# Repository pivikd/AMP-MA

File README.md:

# Project Status

   **AMP-AM is currently in the early development phase and is considered unstable. The first stable release is scheduled for Q4 2026**
   
   **The project is currently in the pre-alpha stage – creating the first prototype**

# AMP-AM (AMP Modus Aequale)

AMP-AM (standing for Modus Aequale, signifying a rhythmic, ideal tone and modular structure) is an open-source, transistor-based guitar combo amplifier project. It is designed to bridge the gap between solid-state reliability and the organic, harmonic richness of vacuum tube sound.

The project focuses on a modular architecture, originally developed as a high-fidelity upgrade for the **Epiphone 15C** PCB. By utilizing independent blocks, AMP-AM allows for seamless customization and easier adaptation to various amp enclosures.

This project is designed and maintained by: [Danylo Pyvovarov](https://github.com/pivikd).

   1. [Key Features](#key-features)
   1. [Signal Chain](#signal-chain)
   1. [Integrated Tone Stacks](#integrated-tone-stacks)
<!-- 1. [Integrated Effects Modules](#integrated-effects-modules) -->
## Key Features
   - **Tube-like Architecture**: Uses **Mu-amp** based cascades with **2SK30A** transistors to achieve a warm, organic sound and harmonic saturation that mimics vacuum tube behavior.

   - **Dual Input Support**: Designed to handle two guitars simultaneously.

   - **Legendary Tone Stacks**: Features a 3-band EQ based on the classic tone stacks([Integrated Tone Stacks](#integrated-tone-stacks)).

   - **Integrated Compression**: Built-in compressor block based on the vintage **Ibanez CP835** circuitry.

   <!-- - **Modular Design**: Optimized for easy integration into different amp cabinets or for swapping internal effect modules. -->

## Signal Chain
   1. Input buffer
   1. Preamp ([Mu-AMP](https://www.muzique.com/amz/mini.htm))
   1. Compressor ([Ibanez CP835](https://www.scribd.com/document/976348354/Ibanez-CP835-Schematic))
   1. Tone Stack
   1. Recovery Stage
   1. Power Amp ([LM1875](https://www.ti.com/lit/ds/symlink/lm1875.pdf))

<!-- ## Integrated Effects Modules
|       Effect      |   based on   |  Status  |
|-------------------|--------------|---------|
| Compressor        | Ibanez CP835 |  done   |
<!-- | Over Drive        | Boss OD3     | planned  |
| Chorus            | Boss Ch1     | planned  | --> 

## Integrated Tone Stacks
   - Fender Treble-Middle-Bass
   - Marshall ([JCM900 2100 SL-X](https://stompboxelectronics.com/2023/12/16/the-marshall-tone-stacks/))
   - Dumble Rock

      Own:
   - TS0 (based on Marshall JCM900 2100 SL-x)
   - TS1 (based on Dumble Rock)

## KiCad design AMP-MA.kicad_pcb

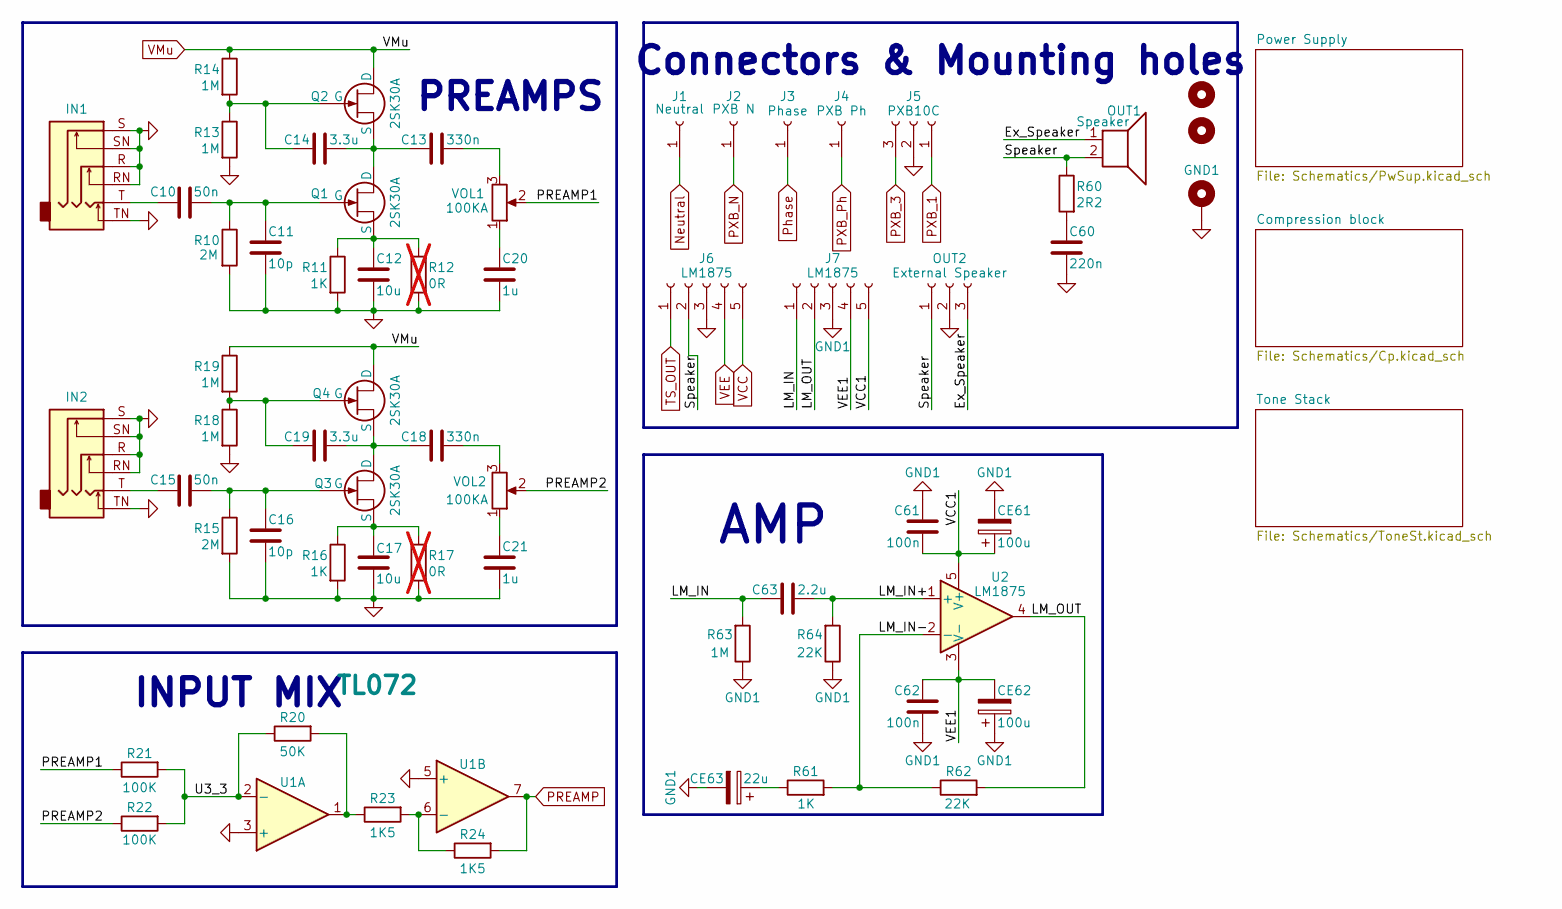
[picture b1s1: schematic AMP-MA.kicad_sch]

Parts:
C10, C15: 50n; C_disc_D7_W2.5_P5
C11, C16: 10p; C_disc_D7_W2.5_P5
C12, C17: 10u; C_disc_D7_W2.5_P5
C13, C18: 330n; C_disc_D7_W2.5_P5
C14, C19: 3.3u; C_disc_D7_W2.5_P5
C20, C21: 1u; C_disc_D7_W2.5_P5
C60: 220n; C_disc_D7_W2.5_P5
C61, C62: 100n; C_disc_D7_W2.5_P5
C63: 2.2u; C_disc_D7_W2.5_P5
CE61, CE62: 100u; CP_Radial_D6.3mm_P2.50mm
CE63: 22u; CP_Radial_D5.0mm_P2.50mm
GND1: MountingHole_Pad; MountingHole_2.2mm_M2_DIN965_Pad
H1, H2: MountingHole; MountingHole_2.2mm_M2
IN1, IN2: Jack_3_6pin
J1: Neutral; connector
J2: PXB N; connector
J3: Phase
J4: PXB Ph
J5: PXB10C; JST_XH_B3B-XH-A_1x03_P2.50mm_Vertical
J6, J7: LM1875; JST_XH_B5B-XH-A_1x05_P2.50mm_Vertical
OUT1: Speaker; PinSocket_1x02_P2.54mm_Vertical
OUT2: External Speaker; JST_XH_B3B-XH-A_1x03_P2.50mm_Vertical
Q1, Q2, Q3, Q4: 2SK30A; TO-92_Inline_Wide
R10, R15: 2M; R_Axial_DIN0207_L6.3mm_D2.5mm_P10.16mm_Horizontal
R11, R16, R61: 1K; R_Axial_DIN0207_L6.3mm_D2.5mm_P10.16mm_Horizontal
R12, R17: 0R; R_Axial_DIN0207_L6.3mm_D2.5mm_P10.16mm_Horizontal; not fitted
R13, R14, R18, R19, R63: 1M; R_Axial_DIN0207_L6.3mm_D2.5mm_P10.16mm_Horizontal
R20: 50K; R_Axial_DIN0207_L6.3mm_D2.5mm_P10.16mm_Horizontal
R21, R22: 100K; R_Axial_DIN0207_L6.3mm_D2.5mm_P10.16mm_Horizontal
R23, R24: 1K5; R_Axial_DIN0207_L6.3mm_D2.5mm_P10.16mm_Horizontal
R60: 2R2; R_Axial_DIN0207_L6.3mm_D2.5mm_P10.16mm_Horizontal
R62, R64: 22K; R_Axial_DIN0207_L6.3mm_D2.5mm_P10.16mm_Horizontal
U1: TL072; DIP-8_W7.62mm
U2: LM1875; TO-220-5_P3.4x3.7mm_StaggerOdd_Lead3.8mm_Vertical
VOL1, VOL2: 100KA; potentiometer

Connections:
/Ex_Speaker: OUT1.1, OUT2.3
/LM_IN: C63.1, J7.1, R63.2
/LM_IN+: C63.2, R64.2, U2.1 (+)
/LM_IN-: R61.2, R62.1, U2.2 (-)
/LM_OUT: J7.2, R62.2, U2.4
/PREAMP1: R21.1, VOL1.2
/PREAMP2: R22.1, VOL2.2
/Speaker: J6.2, OUT1.2, OUT2.1, R60.1
/U3_3: R20.1, R21.2, R22.2, U1.2 (-)
/VCC1: C61.2, CE61.1, J7.5, U2.5 (V+)
/VEE1: C62.1, CE62.2, J7.4, U2.3 (V-)
GND: C11.1, C12.1, C16.1, C17.1, C20.1, C21.1, C60.2, GND1.1 (1_1), IN1.R, IN1.RN, IN1.S, IN1.SN, IN1.TN, IN2.R, IN2.RN, IN2.S, IN2.SN, IN2.TN, J5.2, J6.3, OUT2.2, R10.2, R11.2, R12.2, R13.2, R15.2, R16.2, R17.2, R18.2, U1.3 (+), U1.5 (+); also elsewhere on the board
GND1: C61.1, C62.2, CE61.2, CE62.1, CE63.2, J7.3, R63.1, R64.1
unnamed: C10.1, IN1.T
unnamed: C13.2, VOL1.3
unnamed: C15.1, IN2.T
unnamed: C18.2, VOL2.3
unnamed: C20.2, VOL1.1
unnamed: C21.2, VOL2.1
unnamed: C60.1, R60.2
unnamed: CE63.1, R61.1
unnamed: C13.1, C14.2, Q1.1 (D), Q2.3 (S)
unnamed: C10.2, C11.2, Q1.2 (G), R10.1
unnamed: C12.2, Q1.3 (S), R11.1, R12.1
unnamed: C14.1, Q2.2 (G), R13.1, R14.2
unnamed: C18.1, C19.2, Q3.1 (D), Q4.3 (S)
unnamed: C15.2, C16.2, Q3.2 (G), R15.1
unnamed: C17.2, Q3.3 (S), R16.1, R17.1
unnamed: C19.1, Q4.2 (G), R18.1, R19.2
unnamed: R20.2, R23.1, U1.1
unnamed: R23.2, R24.1, U1.6 (-)
Neutral: J1.1 (Pin_1_1); also elsewhere on the board
PREAMP: R24.2, U1.7; also elsewhere on the board
PXB_1: J5.1; also elsewhere on the board
PXB_3: J5.3; also elsewhere on the board
PXB_N: J2.1 (Pin_1_1); also elsewhere on the board
TS_OUT: J6.1; also elsewhere on the board
VCC: J6.5; also elsewhere on the board
VEE: J6.4; also elsewhere on the board
VMu: Q2.1 (D), Q4.1 (D), R14.1, R19.1; also elsewhere on the board

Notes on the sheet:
PREAMPS
Connectors & Mounting holes
AMP
INPUT MIX

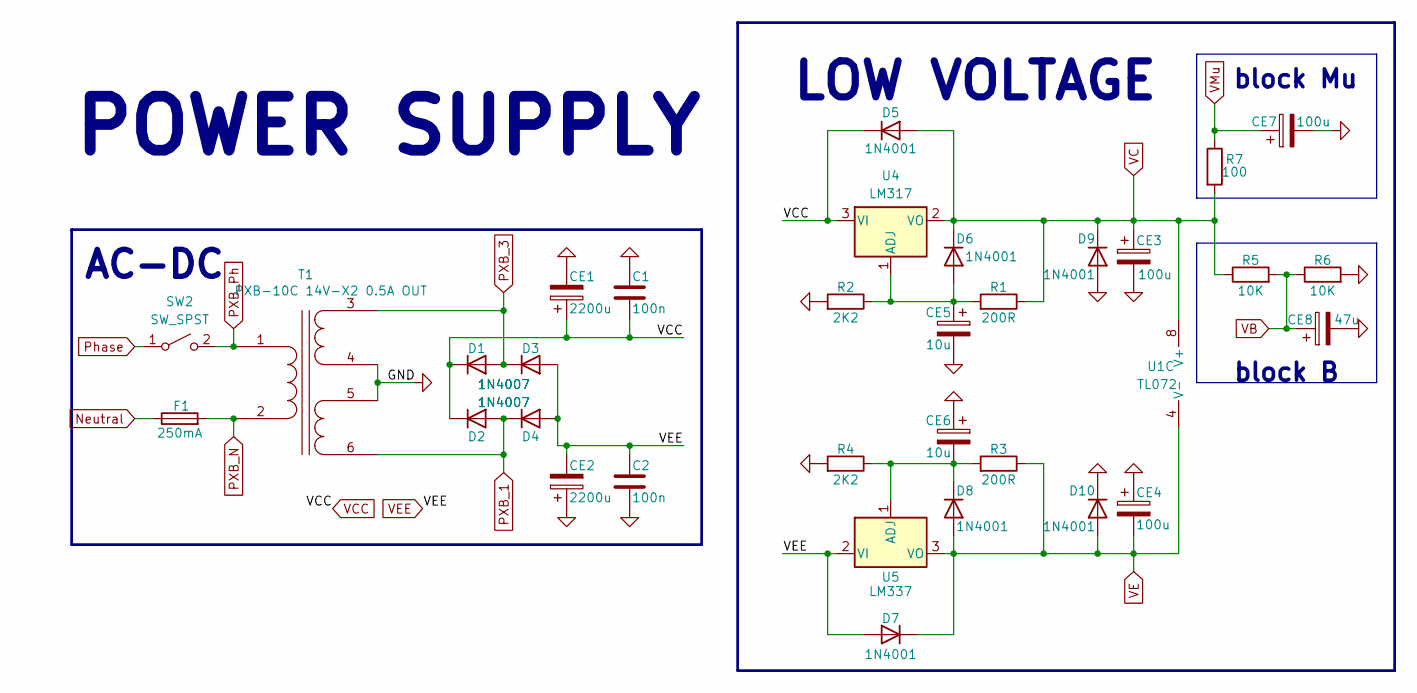
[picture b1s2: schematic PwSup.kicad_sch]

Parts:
C1, C2: 100n; C_disc_D7_W2.5_P5
CE1, CE2: 2200u; CP_Radial_D16.0mm_P7.50mm
CE3, CE4, CE7: 100u; CP_Radial_D6.3mm_P2.50mm
CE5, CE6: 10u; CP_Radial_D6.3mm_P2.50mm
CE8: 47u; CP_Radial_D5.0mm_P2.50mm
D1, D2, D3, D4: 1N4007; D_DO-41_SOD81_P10.16mm_Horizontal
D5, D6, D7, D8, D9, D10: 1N4001; D_DO-41_SOD81_P10.16mm_Horizontal
F1: 250mA; Fuseholder_Clip-5x20mm_Littelfuse_520_Inline_P20.50x5.80mm_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
R1, R3: 200R; R_Axial_DIN0207_L6.3mm_D2.5mm_P10.16mm_Horizontal
R2, R4: 2K2; R_Axial_DIN0207_L6.3mm_D2.5mm_P10.16mm_Horizontal
R5, R6: 10K; R_Axial_DIN0207_L6.3mm_D2.5mm_P10.16mm_Horizontal
R7: 100; R_Axial_DIN0207_L6.3mm_D2.5mm_P10.16mm_Horizontal
SW2: SW_SPST
T1: PXB-10C 14V-X2 0.5A OUT
U1: TL072; DIP-8_W7.62mm
U4: LM317; TO-220-3_Horizontal_TabDown
U5: LM337; TO-220-3_Horizontal_TabDown

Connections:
GND: C1.2, C2.2, CE1.2, CE2.1, CE3.2, CE4.1, CE5.2, CE6.1, CE7.2, CE8.2, D9.2 (A), D10.1 (K), R2.2, R4.2, R6.2, T1.4 (SB), T1.5 (SC); also elsewhere on the board
unnamed: CE5.1, D6.2 (A), R1.2, R2.1, U4.1 (ADJ)
unnamed: CE6.2, D8.1 (K), R3.2, R4.1, U5.1 (ADJ)
unnamed: SW2.2 (B), T1.1 (AA)
Neutral: F1.1; also elsewhere on the board
PXB_1: D2.2 (A), D4.1 (K), T1.6 (SD); also elsewhere on the board
PXB_3: D1.2 (A), D3.1 (K), T1.3 (SA); also elsewhere on the board
PXB_N: F1.2, T1.2 (AB); also elsewhere on the board
VB: CE8.1, R5.2, R6.1; also elsewhere on the board
VC: CE3.1, D5.2 (A), D6.1 (K), D9.1 (K), R1.1, R5.1, R7.2, U1.8 (V+), U4.2 (VO); also elsewhere on the board
VCC: C1.1, CE1.1, D1.1 (K), D2.1 (K), D5.1 (K), U4.3 (VI); also elsewhere on the board
VE: CE4.2, D7.1 (K), D8.2 (A), D10.2 (A), R3.1, U1.4 (V-), U5.3 (VO); also elsewhere on the board
VEE: C2.1, CE2.2, D3.2 (A), D4.2 (A), D7.2 (A), U5.2 (VI); also elsewhere on the board
VMu: CE7.1, R7.1; also elsewhere on the board

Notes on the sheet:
AC-DC
block Mu
block B
LOW VOLTAGE
POWER SUPPLY

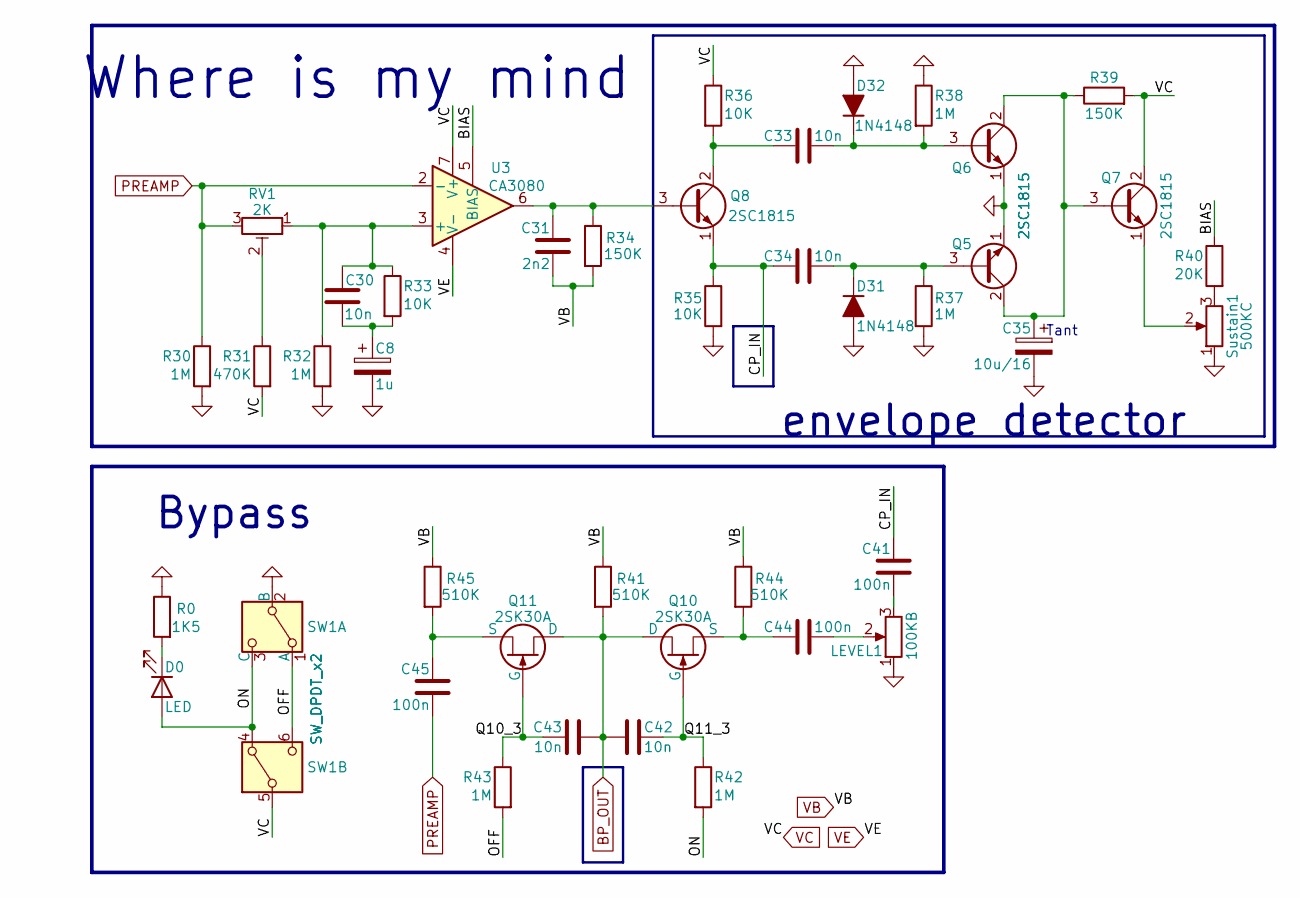
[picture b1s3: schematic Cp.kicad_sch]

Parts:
C8: 1u; C_disc_D7_W2.5_P5
C30: 10n; C_disc_D7_W2.5_P5
C31: 2n2; C_Disc_D4.3_W1.9_P5.00
C33, C34, C42, C43: 10n; C_Disc_D4.3_W1.9_P5.00
C35: 10u/16; CP_Radial_Tantal_D5.5mm_P2.50mm
C41, C44, C45: 100n; C_disc_D7_W2.5_P5
D0: LED; LED_D3.0mm_Horizontal_O6.35mm_Z6.0mm
D31, D32: 1N4148; D_DO-35_SOD27_P7.62mm_Horizontal
LEVEL1: 100KB; Potentiometer_Bourns_3296W_Vertical
Q5, Q6, Q7, Q8: 2SC1815; TO-92_Inline_Wide
Q10, Q11: 2SK30A; TO-92_Inline_Wide
R0: 1K5; R_Axial_DIN0207_L6.3mm_D2.5mm_P10.16mm_Horizontal
R30, R32, R37, R38, R42, R43: 1M; R_Axial_DIN0207_L6.3mm_D2.5mm_P10.16mm_Horizontal
R31: 470K; R_Axial_DIN0207_L6.3mm_D2.5mm_P10.16mm_Horizontal
R33, R35, R36: 10K; R_Axial_DIN0207_L6.3mm_D2.5mm_P10.16mm_Horizontal
R34, R39: 150K; R_Axial_DIN0207_L6.3mm_D2.5mm_P10.16mm_Horizontal
R40: 20K; R_Axial_DIN0207_L6.3mm_D2.5mm_P10.16mm_Horizontal
R41, R44, R45: 510K; R_Axial_DIN0207_L6.3mm_D2.5mm_P10.16mm_Horizontal
RV1: 2K; Potentiometer_Bourns_3296W_Vertical
SW1: SW_DPDT_x2; SW DPDT
Sustain1: 500KC; potentiometer
U3: CA3080; DIP-8_W7.62mm

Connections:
/Compression block/BIAS: R40.1, U3.5 (BIAS)
/Compression block/CP_IN: C34.1, C41.2, Q8.1 (E), R35.1
/Compression block/OFF: R43.2, SW1.1 (A), SW1.6 (C)
/Compression block/ON: D0.2 (A), R42.2, SW1.3 (C), SW1.4 (A)
/Compression block/Q10_3: C43.2, Q11.2 (G), R43.1
/Compression block/Q11_3: C42.1, Q10.2 (G), R42.1
BP_OUT: C42.2, C43.1, Q10.1 (D), Q11.1 (D), R41.2; also elsewhere on the board
GND: C8.2, C35.2, D31.2 (A), D32.2 (A), LEVEL1.1, Q5.1 (E), Q6.1 (E), R0.1, R30.2, R32.2, R35.2, R37.2, R38.1, SW1.2 (B), Sustain1.1; also elsewhere on the board
unnamed: C8.1, C30.2, R33.2
unnamed: C41.1, LEVEL1.3
unnamed: C44.2, LEVEL1.2
unnamed: D0.1 (K), R0.2
unnamed: C34.2, D31.1 (K), Q5.3 (B), R37.1
unnamed: C33.2, D32.1 (K), Q6.3 (B), R38.2
unnamed: C35.1, Q5.2 (C), Q6.2 (C), Q7.3 (B), R39.1
unnamed: Q7.1 (E), Sustain1.2
unnamed: C31.1, Q8.3 (B), R34.1, U3.6
unnamed: C33.1, Q8.2 (C), R36.2
unnamed: C44.1, Q10.3 (S), R44.2
unnamed: C45.2, Q11.3 (S), R45.2
unnamed: R31.1, RV1.2
unnamed: R40.2, Sustain1.3
unnamed: C30.1, R32.1, R33.1, RV1.1, U3.3 (+)
PREAMP: C45.1, R30.1, RV1.3, U3.2 (-); also elsewhere on the board
VB: C31.2, R34.2, R41.1, R44.1, R45.1; also elsewhere on the board
VC: Q7.2 (C), R31.2, R36.1, R39.2, SW1.5 (B), U3.7 (V+); also elsewhere on the board
VE: U3.4 (V-); also elsewhere on the board

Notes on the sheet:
Bypass
envelope detector
Tant
Where is my mind

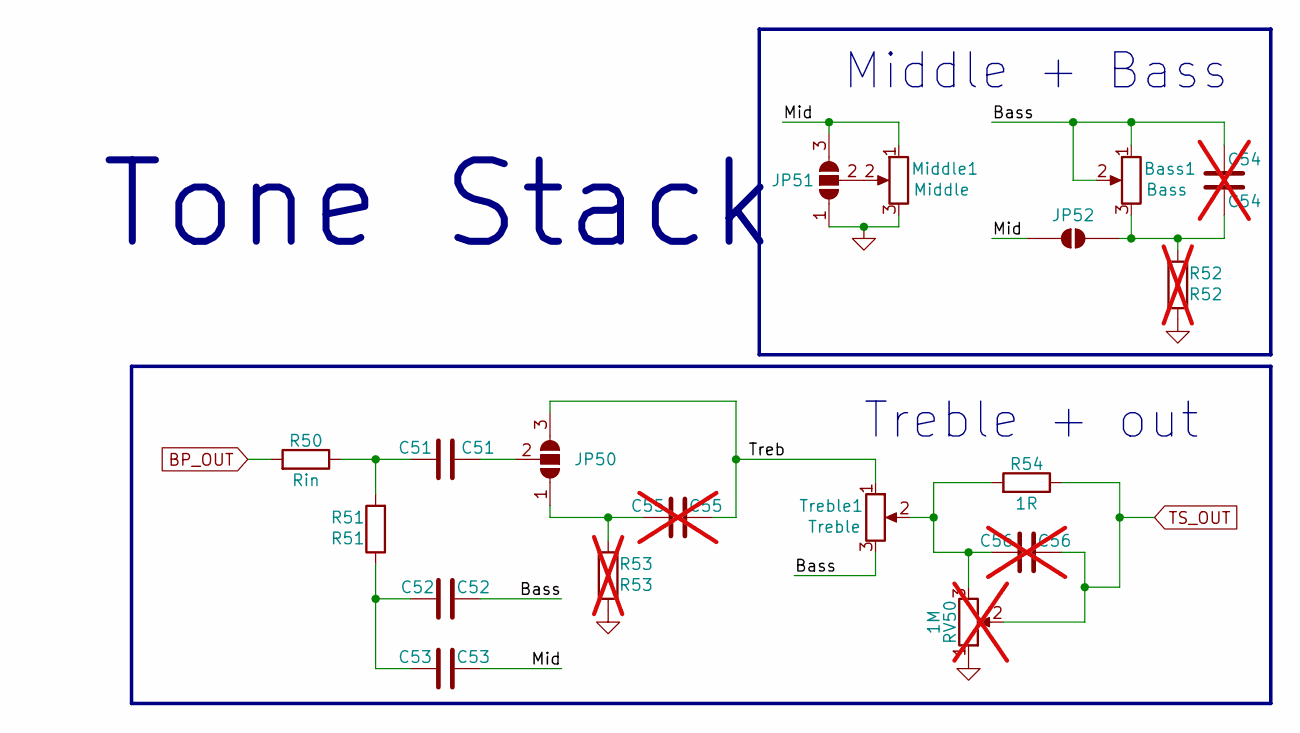
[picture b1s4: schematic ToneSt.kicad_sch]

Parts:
Bass1: Bass; potentiometer
C51: C51; C_disc_D7_W2.5_P5
C52: C52; C_disc_D7_W2.5_P5
C53: C53; C_disc_D7_W2.5_P5
C54: C54; C_disc_D7_W2.5_P5; not fitted
C55: C55; C_disc_D7_W2.5_P5; not fitted
C56: C56; C_disc_D7_W2.5_P5; not fitted
JP50, JP51: SolderJumper_3_Open; SolderJumper-3_P2.0mm_Open_TrianglePad1.0x1.5mm_NumberLabels
JP52: SolderJumper_2_Open; SolderJumper-2_P1.3mm_Open_TrianglePad1.0x1.5mm
Middle1: Middle; potentiometer
R50: Rin; R_Axial_DIN0207_L6.3mm_D2.5mm_P10.16mm_Horizontal
R51: R51; R_Axial_DIN0207_L6.3mm_D2.5mm_P10.16mm_Horizontal
R52: R52; R_Axial_DIN0207_L6.3mm_D2.5mm_P10.16mm_Horizontal; not fitted
R53: R53; R_Axial_DIN0207_L6.3mm_D2.5mm_P10.16mm_Horizontal; not fitted
R54: 1R; R_Axial_DIN0207_L6.3mm_D2.5mm_P10.16mm_Horizontal
RV50: 1M; Potentiometer_Bourns_3296W_Vertical; not fitted
Treble1: Treble; potentiometer

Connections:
/Tone Stack/Bass: Bass1.1, Bass1.2, C52.2, C54.2, Treble1.3
/Tone Stack/Mid: C53.2, JP51.3 (B), JP52.1 (A), Middle1.1
/Tone Stack/Treb: C55.2, JP50.3 (B), Treble1.1
BP_OUT: R50.2; also elsewhere on the board
GND: JP51.1 (A), Middle1.3, R52.1, R53.1, RV50.1; also elsewhere on the board
unnamed: C51.1, R50.1, R51.2
unnamed: C52.1, C53.1, R51.1
unnamed: C56.1, R54.2, RV50.3, Treble1.2
unnamed: C55.1, JP50.1 (A), R53.2
unnamed: C51.2, JP50.2 (C)
unnamed: JP51.2 (C), Middle1.2
unnamed: Bass1.3, C54.1, JP52.2 (B), R52.2
TS_OUT: C56.2, R54.1, RV50.2; also elsewhere on the board

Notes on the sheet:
Tone Stack
Middle + Bass
Treble + out

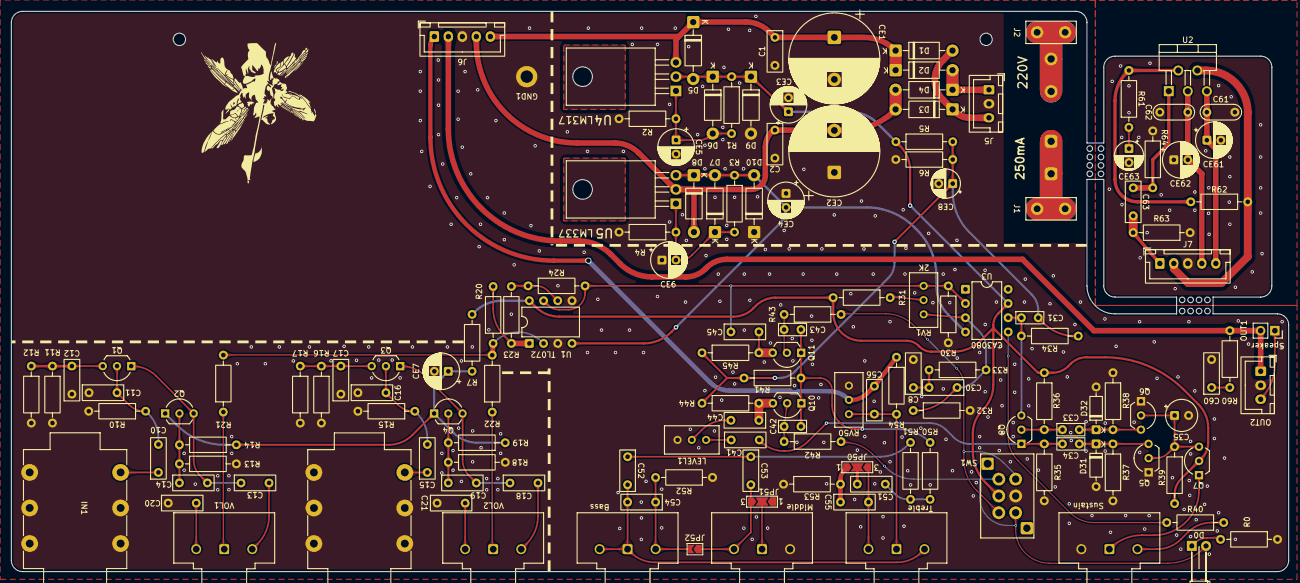
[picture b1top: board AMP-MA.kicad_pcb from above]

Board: 2 copper layers, 228.0 x 100.0 mm, 149 parts (1 on the bottom side), 77 nets.

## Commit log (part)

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2026-04-23 Init commit
2026-04-23 Schem upd
    added Copressor module
2026-04-24 Schem upd
    added Voltage supply
2026-04-25 added own library
2026-04-26 Schem & lib upd
    added audiojack symbol & added PREAMP cascade
2026-04-27 ReadME upd
2026-04-27 Project renamed
2026-04-28 Schem & Lib upd
    Lib: added footprint and Symbol foe new 6pin jack Schem: changed jacks
2026-04-29 Schem upd
    Tone Stack addded
2026-04-30 Schem & README upd
    added AMP block
2026-05-02 power supply upd
    9v pover supply changed on AC-DC tancformer
2026-05-03 Big upd
    moved hierarical Sheets to direсtory Schematics, revorked power supply
2026-05-03 footprints assigned
2026-05-04 directory cleared, Schem upd
    The input mixer changed from passive to active(TL072)
2026-05-05 Schem upd
    in bypass button changed on SPDT switch
2026-05-06 Schem upd
    The LED is powered by the low voltage supply, not by the effect
2026-05-06 Schem upd
    Managed power supply for TL072
2026-05-07 Schem upd & added .gitignore
2026-05-11 Lib & Schematic upd
    Jack connector symbol update. Made basic layout has been made
2026-05-18 smal schem upd

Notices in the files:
README.md:
License: GPL-3.0
